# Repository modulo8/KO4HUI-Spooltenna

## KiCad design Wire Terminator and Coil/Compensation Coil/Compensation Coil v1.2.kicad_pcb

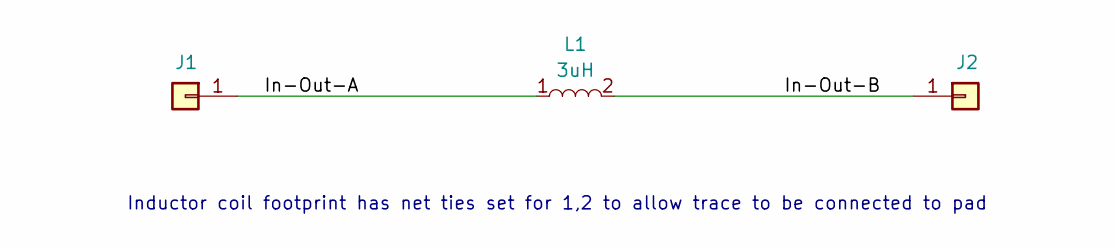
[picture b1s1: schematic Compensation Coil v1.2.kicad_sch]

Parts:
J1, J2: Conn_01x01; SMD-WIRE-CONNECTOR-4BY2
L1: 3uH; COIL-3UH-2LAYER-0P8W-0P4S

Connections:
/In-Out-A: J1.1, L1.1
/In-Out-B: J2.1, L1.2

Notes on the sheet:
Inductor coil footprint has net ties set for 1,2 to allow trace to be connected to pad

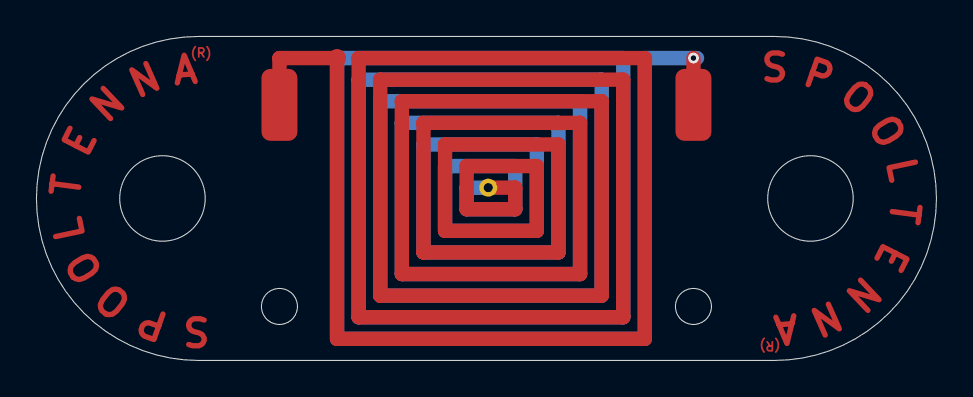
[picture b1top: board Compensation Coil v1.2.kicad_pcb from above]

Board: 2 copper layers, 50.0 x 18.0 mm, 3 parts (0 on the bottom side), 2 nets.

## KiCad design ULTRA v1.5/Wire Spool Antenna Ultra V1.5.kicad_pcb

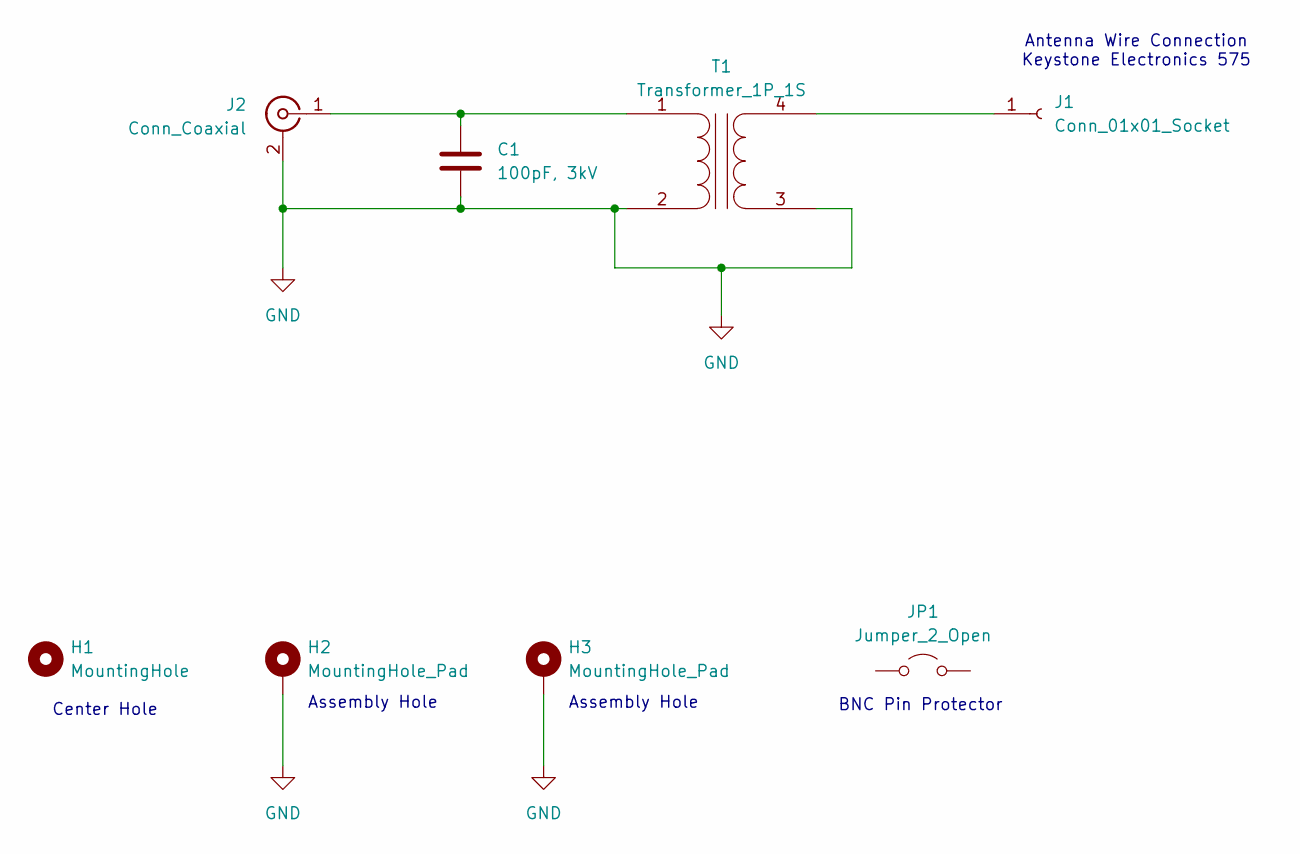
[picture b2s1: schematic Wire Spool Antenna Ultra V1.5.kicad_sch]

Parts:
C1: 100pF, 3kV; C_Disc_D8.5mm_W5.5mm_P7.50mm
H1: MountingHole; MountingHole_8.4mm_M8
H2, H3: MountingHole_Pad; MountingHole_3.2mm_M3_Pad_TopBottom
J1: Conn_01x01_Socket; Banana_Jack_Keystone_575
J2: Conn_Coaxial; BNC_MOLEX_73100_PIPE_WIDE
JP1: Jumper_2_Open; Jumper Loop 12AWG
T1: Transformer_1P_1S; TOROID_140_AUTO_COMPACT_30

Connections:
GND: C1.2, H2.1, H3.1, J2.2 (Ext), T1.2 (AB), T1.3 (SA)
unnamed: J1.1, T1.4 (SB)
unnamed: C1.1, J2.1 (In), T1.1 (AA)

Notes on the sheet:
Assembly Hole
Antenna Wire Connection Keystone Electronics 575
Center Hole
BNC Pin Protector

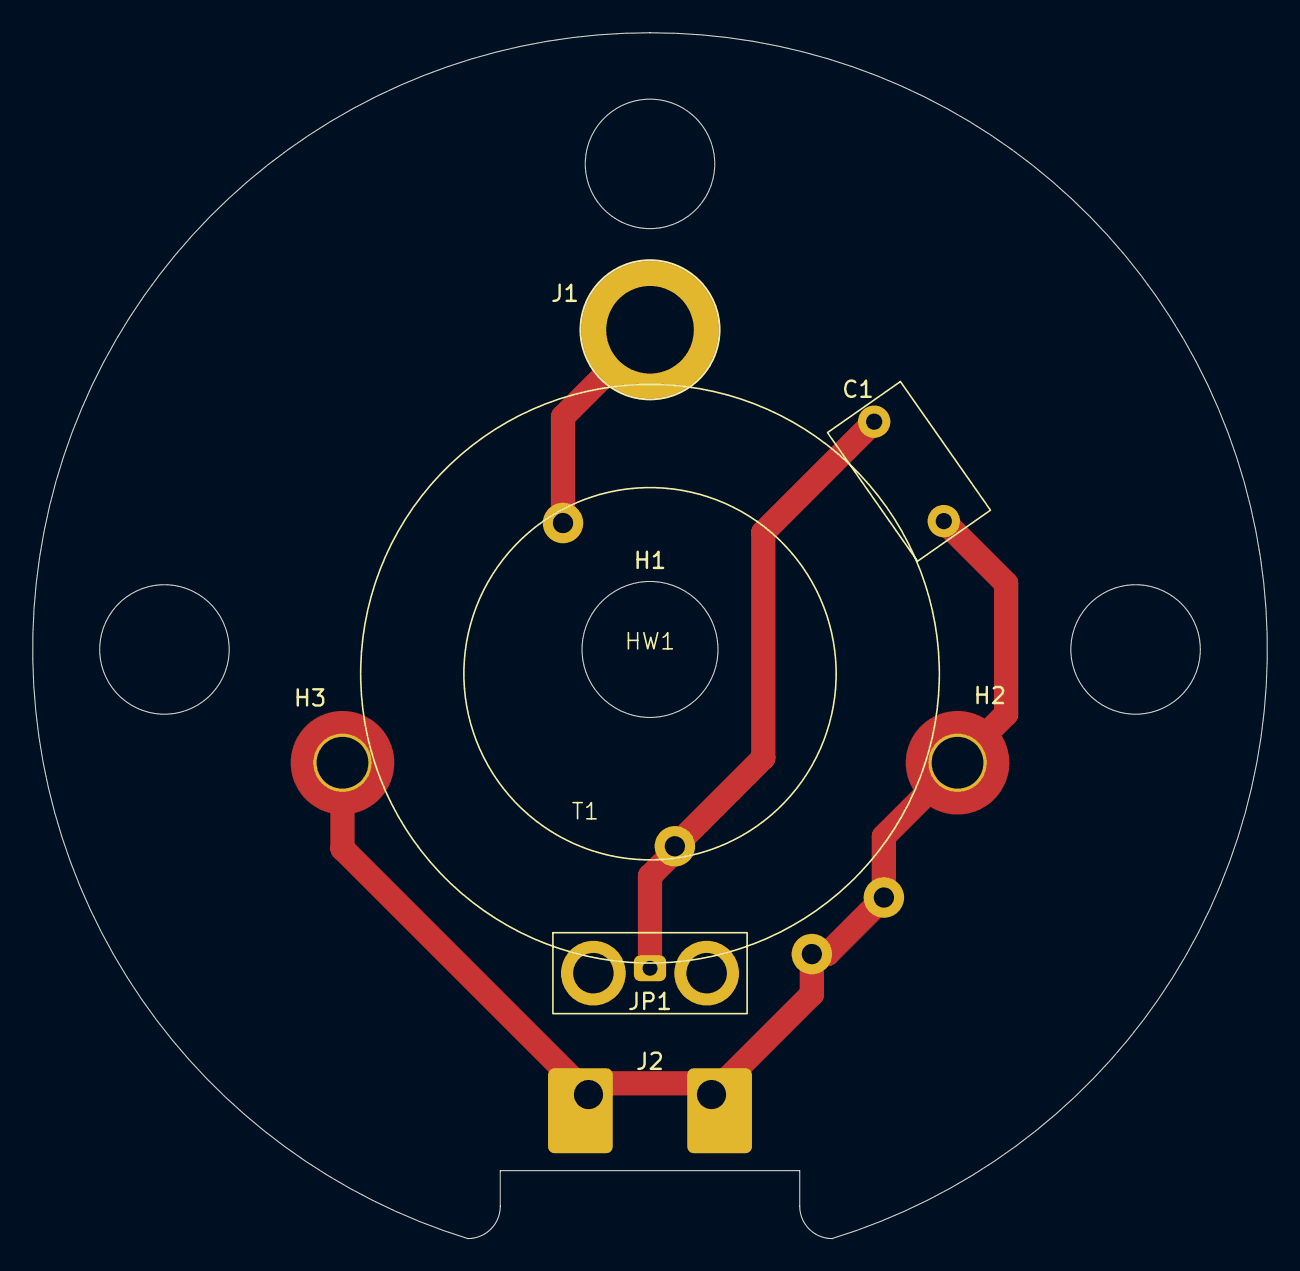
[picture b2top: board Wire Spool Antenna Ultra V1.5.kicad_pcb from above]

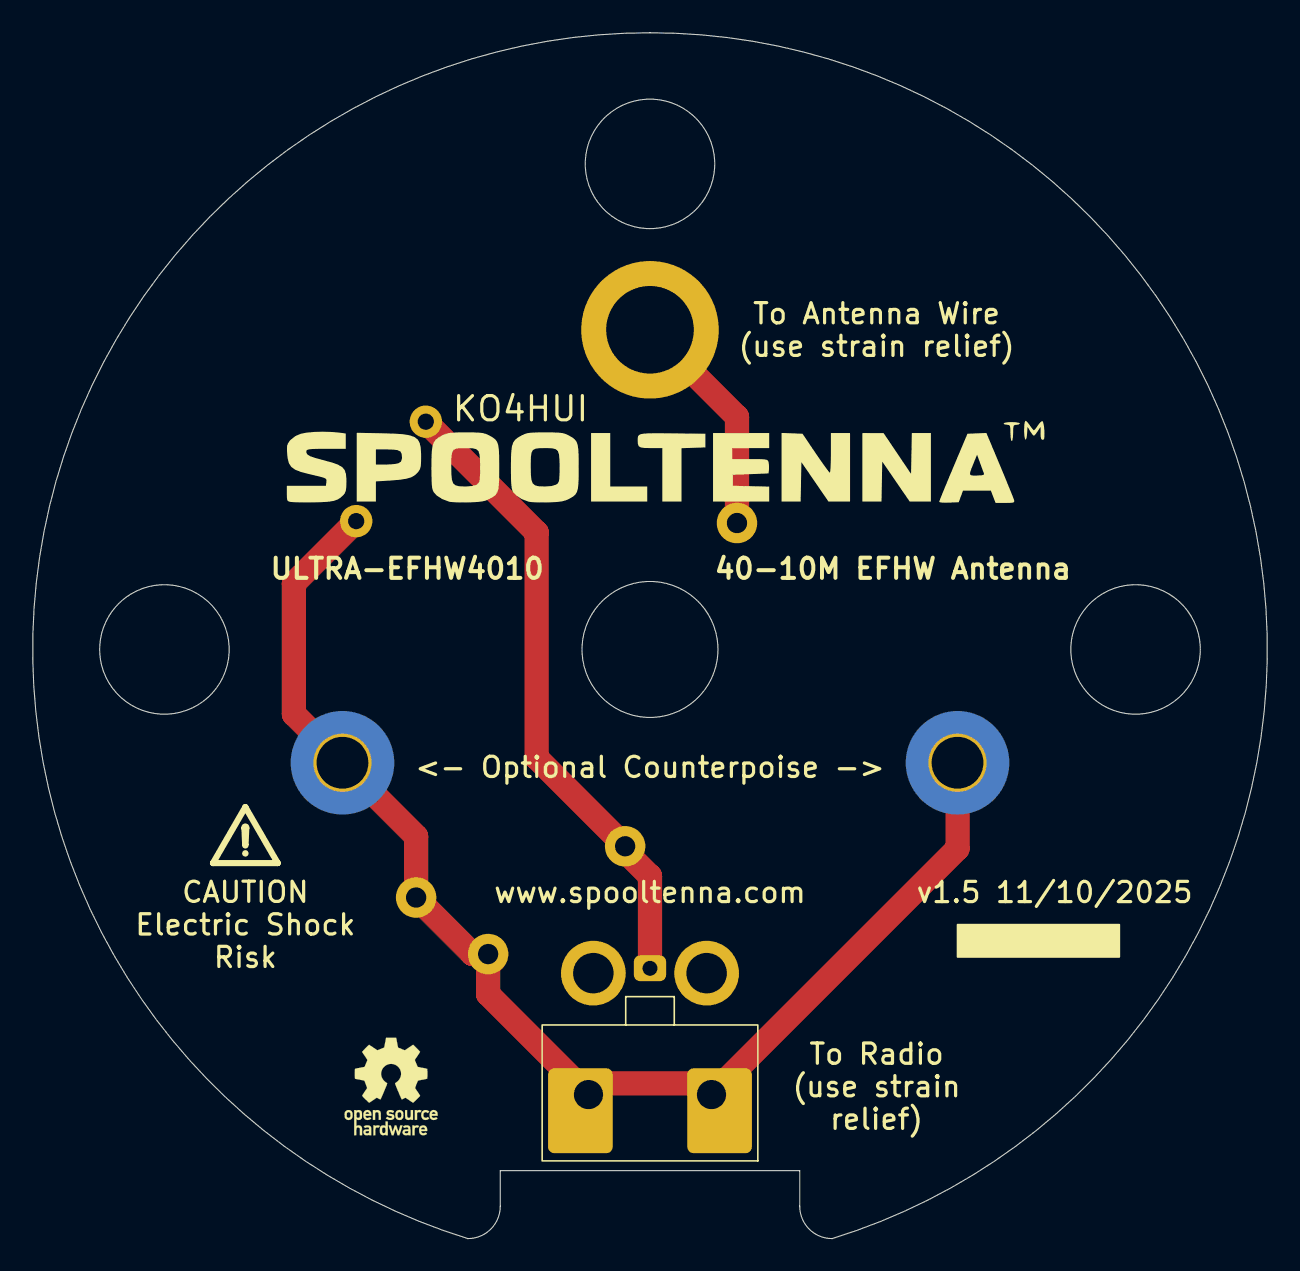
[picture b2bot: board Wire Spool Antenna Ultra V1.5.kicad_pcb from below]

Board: 2 copper layers, 76.3 x 74.5 mm, 10 parts (2 on the bottom side), 3 nets.

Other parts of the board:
HW1: Fiberglass Barrel 2 Inch OD
HW1#2: JLCPCB Serial Number Only
